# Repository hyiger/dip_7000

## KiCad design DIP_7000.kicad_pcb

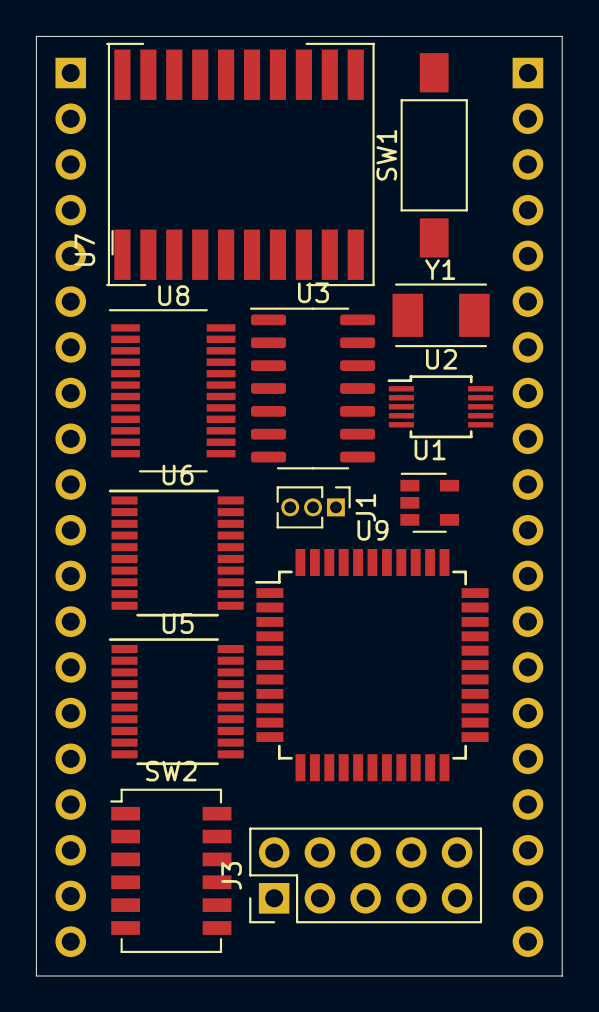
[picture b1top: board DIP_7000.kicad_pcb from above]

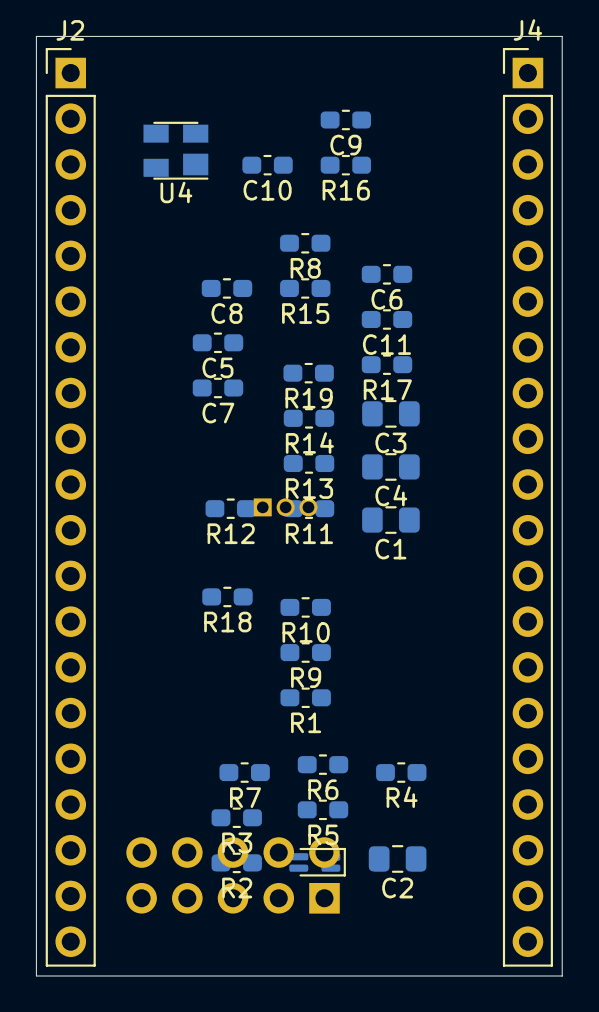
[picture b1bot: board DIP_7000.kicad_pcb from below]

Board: 2 copper layers, 29.2 x 52.2 mm, 47 parts (34 on the bottom side), 84 nets, no tracks yet.

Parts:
C1: 22uF; C_0805_2012Metric_Pad1.15x1.40mm_HandSolder
C2: 10uF; C_0805_2012Metric_Pad1.15x1.40mm_HandSolder
C3, C4: 100nF; C_0805_2012Metric_Pad1.15x1.40mm_HandSolder
C5, C6: 0.47uF; C_0603_1608Metric_Pad1.05x0.95mm_HandSolder
C7, C8, C9, C10, C11: 100nF; C_0603_1608Metric_Pad1.05x0.95mm_HandSolder
D1: Red/Green; LED_2C_0603_1608Metric_Pad1.05x0.95mm_HandSolder
J1: UPDI TTL; PinHeader_1x03_P1.27mm_Vertical
J2, J4: Conn_01x20; PinHeader_1x20_P2.54mm_Vertical
J3: AVR-JTAG-10; PinHeader_2x05_P2.54mm_Vertical
R1, R2, R5: 1K; R_0603_1608Metric_Pad1.05x0.95mm_HandSolder
R3: 4K7; R_0603_1608Metric_Pad1.05x0.95mm_HandSolder
R4: 9.53K; R_0603_1608Metric_Pad1.05x0.95mm_HandSolder
R6, R7, R8, R9, R10, R11, R12, R13, R14, R17, R18, R19: 10K; R_0603_1608Metric_Pad1.05x0.95mm_HandSolder
R15, R16: 680R; R_0603_1608Metric_Pad1.05x0.95mm_HandSolder
SW1: SW_Push; SW_SPST_FSMSM
SW2: SW_DIP_x06; SW_DIP_SPSTx06_Slide_Copal_CHS-06A_W5.08mm_P1.27mm_JPin
U1: TPS7A0533PDBVR; SOT-23-5
U2: Si5351A-B-GT; MSOP-10_3x3mm_P0.5mm
U3: ATtiny1614-SS; SOIC-14_3.9x8.7mm_P1.27mm
U4: MIC811LUY; SOT-143
U5: 74HCT240; TSSOP-20_4.4x6.5mm_P0.65mm
U6: 74HCT541; TSSOP-20_4.4x6.5mm_P0.65mm
U7: ACDA02-41SGWA-F01
U8: AS1115-BSST; QSOP-24_3.9x8.7mm_P0.635mm
U9: CPLD - EPM7032STC44; TQFP-44_10x10mm_P0.8mm
Y1: 25MHZ 8PF; Crystal_SMD_TXC_7A-2Pin_5x3.2mm

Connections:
+3V3: C1.1, C3.1, C4.1, C5.1, C6.1, R1.1, R2.1, R4.1, U1.5, U2.1, U2.7, U3.1, U6.20, U8.19
+5V: C2.1, C3.2, C4.2, C7.1, C8.1, C9.1, C10.1, C11.1, J3.4, J3.6, R9.2, R10.2, R11.2, R12.2, R13.2, R14.2, R15.2, R16.2, U1.1, U1.3, U4.4, U5.20, U9.9, U9.17, U9.29, U9.41
/A: U7.12, U7.17, U8.15
/A1: J2.3, U9.42
/A2: J2.4, U9.43
/A3: J2.5, U9.44
/A5: J2.6, U9.2
/A6: J2.7, U9.3
/A7: J2.8, U9.5
/A8: J2.9, U9.6
/A10: J2.10, U9.8
/A11: J2.11, U9.10
/A12: J2.12, U9.11
/A13: J2.13, U9.12
/A14: J2.14, U9.13
/A15: J2.15, U9.14
/A16: J2.16, U9.15
/B: U7.11, U7.16, U8.17
/B17: J4.2, U9.35
/B18: J4.3, U9.34
/B19: J4.4, U9.33
/B21: J4.5, U9.31
/B22: J4.6, U9.30
/B23: J4.7, U9.28
/B24: J4.8, U9.27
/B26: J4.9, U9.25
/C: U7.4, U7.9, U8.20
/CLK0: U2.10, U5.2
/CLK1: U2.9, U5.4
/CLK2: U2.6, U5.6
/CLK_100: U5.18, U9.37
/CLR: J2.18, R18.2, U9.39
/D: U7.2, U7.7, U8.23
/D0: J4.10, U6.2
/D1: J4.11, U6.3
/D2: J4.12, U6.4
/D3: J4.13, U6.5
/D4: J4.14, U6.6
/D5: J4.15, U6.7
/D6: J4.16, U6.8
/D7: J4.17, U6.9
/DIG0: U7.3, U7.18, U8.2
/DIG1: U7.8, U7.13, U8.3
/DP: U7.5, U7.10, U8.22
/E: U7.1, U7.6, U8.21
/F: U7.14, U7.19, U8.16
/G: U7.15, U7.20, U8.18
/GRN: D1.4, U5.5
/IRQ: U3.6, U8.24
/LED: J2.19, U5.17
/OE1: J2.17, J4.18, R17.2, U9.38
/OE2: R19.2, U9.40
/PA1: U3.11, U6.18
/PA2: U3.12, U6.17
/PA3: U3.13, U6.16
/PA4: U3.2, U6.15
/PA5: U3.3, U6.14
/PA6: U3.4, U6.13
/PA7: U3.5, U6.12
/PB2: U3.7, U6.11
/RED: D1.2, U5.3, U5.15
/RX: J1.3, R3.2, U3.10
/SCL: R1.2, U2.4, U3.9, U8.14
/SDA: R2.2, U2.5, U3.8, U8.1
/SW2_0: R9.1, SW2.12, U9.23
/SW2_1: R10.1, SW2.11, U9.22
/SW2_2: R11.1, SW2.10, U9.21
/SW2_3: R12.1, SW2.9, U9.20
/SW2_4: R13.1, SW2.8, U9.19
/SW2_5: R14.1, SW2.7, U9.18
/TCK: J3.1, R5.2, U9.26
/TDI: J3.9, R8.2, U9.1
/TDO: J3.3, R7.2, U9.32
/TMS: J3.5, R6.2, U9.7
/TX: J1.2, R3.1
/~LED_EN: J2.20, J4.19, U5.19
GND: C1.2, C2.2, C5.2, C6.2, C7.2, C8.2, C9.2, C10.2, C11.2, J1.1, J2.1, J3.2, J3.10, J4.20, R5.1, R17.1, R18.1, R19.1, SW1.1, SW2.1, SW2.2, SW2.3, SW2.4, SW2.5, SW2.6, U1.2, U2.8, U3.14, U4.1, U5.10, U6.10, U8.6, U9.4, U9.16, U9.24, U9.36
unnamed: D1.1, R15.1
unnamed: D1.3, R16.1
unnamed: R4.2, U8.13
unnamed: R6.1, R7.1, R8.1
unnamed: SW1.2, U4.3
unnamed: U2.2, Y1.1
unnamed: U2.3, Y1.2

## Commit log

2019-07-12 initial version
